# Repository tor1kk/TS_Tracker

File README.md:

# TheftShield_Tracker - GPS tracker with SMS communication 

## Brief

TheftShield Tracker is a device designed to provide real-time tracking and monitoring capabilities for valuable assets or vehicles. It leverages the power of GPS technology, GSM communication, and a microcontroller to offer a comprehensive solution for theft prevention and location tracking.

## Usage Instructions

To use the TheftShield Tracker, follow these steps:

1. **Insert SIM Card**:
    - Insert a nano SIM card into the SIM card slot of the device. Ensure that the SIM card does not have a PIN code set.

2. **Restart the Module**:
    - Restart the module by shorting the NRST and GND pins. This will reset the device and prepare it for operation.

3. **Wait for GPS Initialization**:
    - After restarting, the module will wait until the GPS module acquires a valid location fix. This might take a few minutes, especially in a new location or if the device has been off for a long time.

4. **GSM Module Network Registration**:
    - The GSM module will begin registering with the network. You can monitor the registration process by observing the LED indicator on the module:
        - **Fast blinking** (once every second): The module is searching for or trying to connect to a network.
        - **Slow blinking** (once every 3 seconds): The module is connected to the network.

5. **Send Commands**:
    - Once the device is connected to the network, you can start sending SMS commands to it. Note that the first command you send is usually ignored, so you might need to send it a second time.
    
## Features

The TheftShield Tracker offers the following key features:

- **GPS Tracking**: The device is equipped with a NEO-6M GPS module from u-blox, allowing it to accurately determine its geographic coordinates (latitude and longitude). The NEO-6M is a high-performance GPS receiver with excellent sensitivity and low power consumption.
- **GSM Communication**: The SIM800C GSM module from SIMCOM enables the device to send and receive SMS messages, facilitating remote control and data transmission. The SIM800C is a quad-band GSM/GPRS module that supports voice, SMS, and data transfer.
- **Real-Time Location Updates**: Upon receiving an SMS command, the device can promptly send its current GPS coordinates to a specified phone number.
- **Battery Voltage Monitoring**: The device can measure and report the battery voltage level to a specified phone number, ensuring timely monitoring of the power supply. It uses the built-in Analog-to-Digital Converter (ADC) of the STM32F401RCT6 microcontroller to measure the battery voltage.
- **RTC Alarm Configuration**: Users can set an alarm time through an SMS command. When the alarm triggers, the device will automatically send its GPS coordinates to a predefined phone number. The device utilizes the Real-Time Clock (RTC) peripheral of the STM32F401RCT6 microcontroller to set and manage the alarm.
- **Alarm Time Management**: The device allows users to request the current configured alarm time or deactivate the alarm through SMS commands.
- **Power Management**: The device can enter low-power sleep mode when idle, conserving battery life and extending operational duration. The STM32F401RCT6 microcontroller supports various low-power modes, allowing the device to minimize power consumption when not actively performing tasks.

**Here's a table of the supported SMS commands:**

| Command              | Format           | Description                                                                                         |
|----------------------|------------------|-----------------------------------------------------------------------------------------------------|
| Get GPS Coordinates  | 1:               | Sends the device's current GPS coordinates to the specified phone number.                           |
| Get Voltage          | 2:               | Sends the battery voltage level to the specified phone number.                                      |
| Set Alarm Time       | 3:time:          | Sets the RTC alarm time in 24-hour format (e.g., 3:2359: for 11:59 PM). The device will send GPS coordinates to the specified phone number when the alarm triggers. |
| Get Alarm Time       | 4:               | Requests the currently configured RTC alarm time.                                                   |
| Deactivate Alarm     | 5:               | Deactivates the RTC alarm.                                                                          |

The device is powered by a backup battery and incorporates power management features to extend its operational lifetime. It utilizes the FreeRTOS real-time operating system to manage tasks and ensure efficient resource allocation.

With its combination of GPS tracking, GSM communication, and remote control capabilities, the TheftShield Tracker offers a reliable and versatile solution for asset tracking, theft prevention, and location monitoring applications.

## Photos

### 3D Model

### Real PCB

<br/> 

# Project Structure

The project is organized into two main parts:

TheftShield_Tracker/<br/>
├── hardware/<br/>
│ └── README.md<br/>
└── software/<br/>
│└── README.md<br/>
└──
### hardware/
- **README.md**: Contains information about the hardware design.

### software/
- **README.md**: Contains information about the software implementation.

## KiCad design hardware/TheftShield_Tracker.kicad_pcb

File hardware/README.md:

# Hardware

## Brief

This directory contains the hardware design files for the TheftShield_Tracker project. The project utilizes the following key components:

**Microcontroller**

- STM32F401RCT6 - An ARM Cortex-M4 32-bit microcontroller from STMicroelectronics. It serves as the main control unit, handling task scheduling, communication with peripherals, and executing the application logic.

**GPS Module**

- NEO-6M - A high-performance GPS receiver module from u-blox. It provides accurate positioning data and enables tracking capabilities.

**GSM/GPRS Module**

- SIM800C - A quad-band GSM/GPRS module from SIMCOM. It enables SMS communication for remote control and data transmission.

**Other Components**

- MCP1700 - A low-dropout voltage regulator for providing a stable 3.3V supply.
- Backup battery holder and protection circuitry.
- Assorted passive components (resistors, capacitors, etc.).

## Design Files

- The KiCad project files containing the complete hardware design.
- [GPS tracker schematic](./TheftShield_Tracker.pdf) - A PDF version of the schematic.

## Block diagram

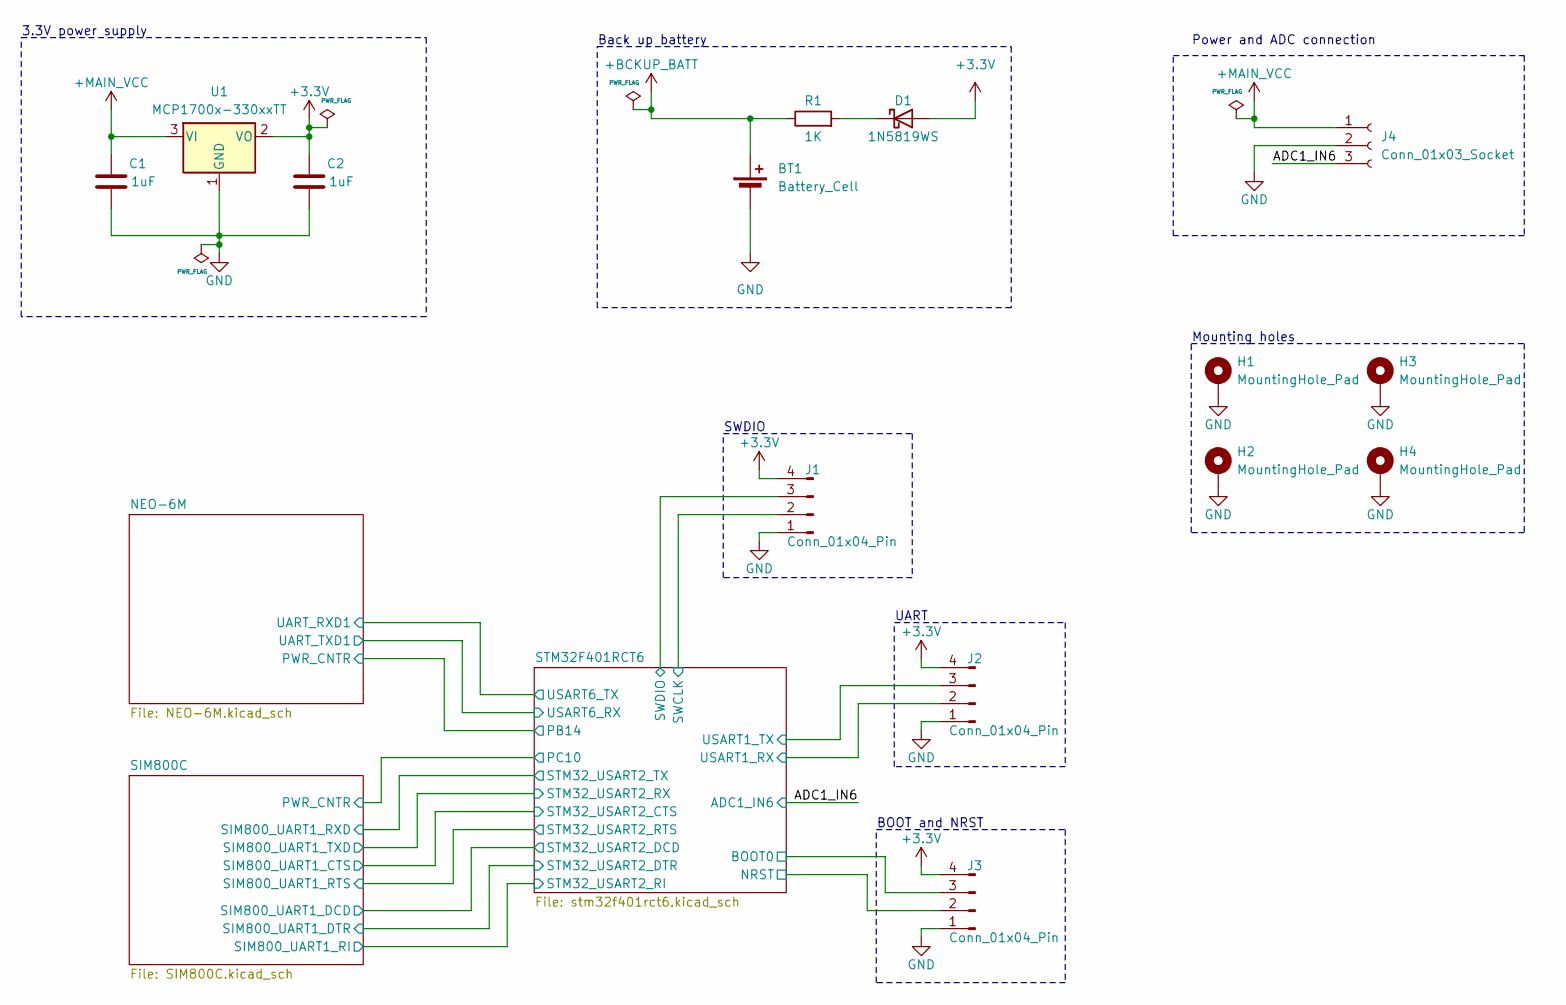
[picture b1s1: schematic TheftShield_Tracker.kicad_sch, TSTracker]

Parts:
BT1: Battery_Cell; SEIKO_ML414H_IV01E
C1, C2: 1uF; C_0805_2012Metric
D1: 1N5819WS; D_SOD-323
H1, H2, H3, H4: MountingHole_Pad; MountingHole_2.2mm_M2_Pad
J1, J2, J3: Conn_01x04_Pin; PinHeader_1x04_P2.54mm_Vertical
J4: Conn_01x03_Socket; JST_XH_B3B-XH-AM_1x03_P2.50mm_Vertical
R1: 1K; R_0603_1608Metric
U1: MCP1700x-330xxTT; SOT-23

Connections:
+3.3V: C2.2, D1.2 (A), J1.4, J2.4, J3.4, U1.2 (VO); also elsewhere on the board
+BCKUP_BATT: BT1.1 (+), R1.1; also elsewhere on the board
+MAIN_VCC: C1.2, J4.1, U1.3 (VI); also elsewhere on the board
/ADC1_IN6: J4.3; also elsewhere on the board
/STM32F401RCT6/BOOT0: J3.3; also elsewhere on the board
/STM32F401RCT6/NRST: J3.2; also elsewhere on the board
/STM32F401RCT6/SWCLK: J1.2; also elsewhere on the board
/STM32F401RCT6/SWDIO: J1.3; also elsewhere on the board
/STM32F401RCT6/USART1_RX: J2.2; also elsewhere on the board
/STM32F401RCT6/USART1_TX: J2.3; also elsewhere on the board
GND: BT1.2 (-), C1.1, C2.1, H1.1, H2.1, H3.1, H4.1, J1.1, J2.1, J3.1, J4.2, U1.1 (GND); also elsewhere on the board
unnamed: D1.1 (K), R1.2

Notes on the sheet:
Power and ADC connection
BOOT and NRST
Mounting holes
SWDIO
Back up battery
3.3V power supply
UART

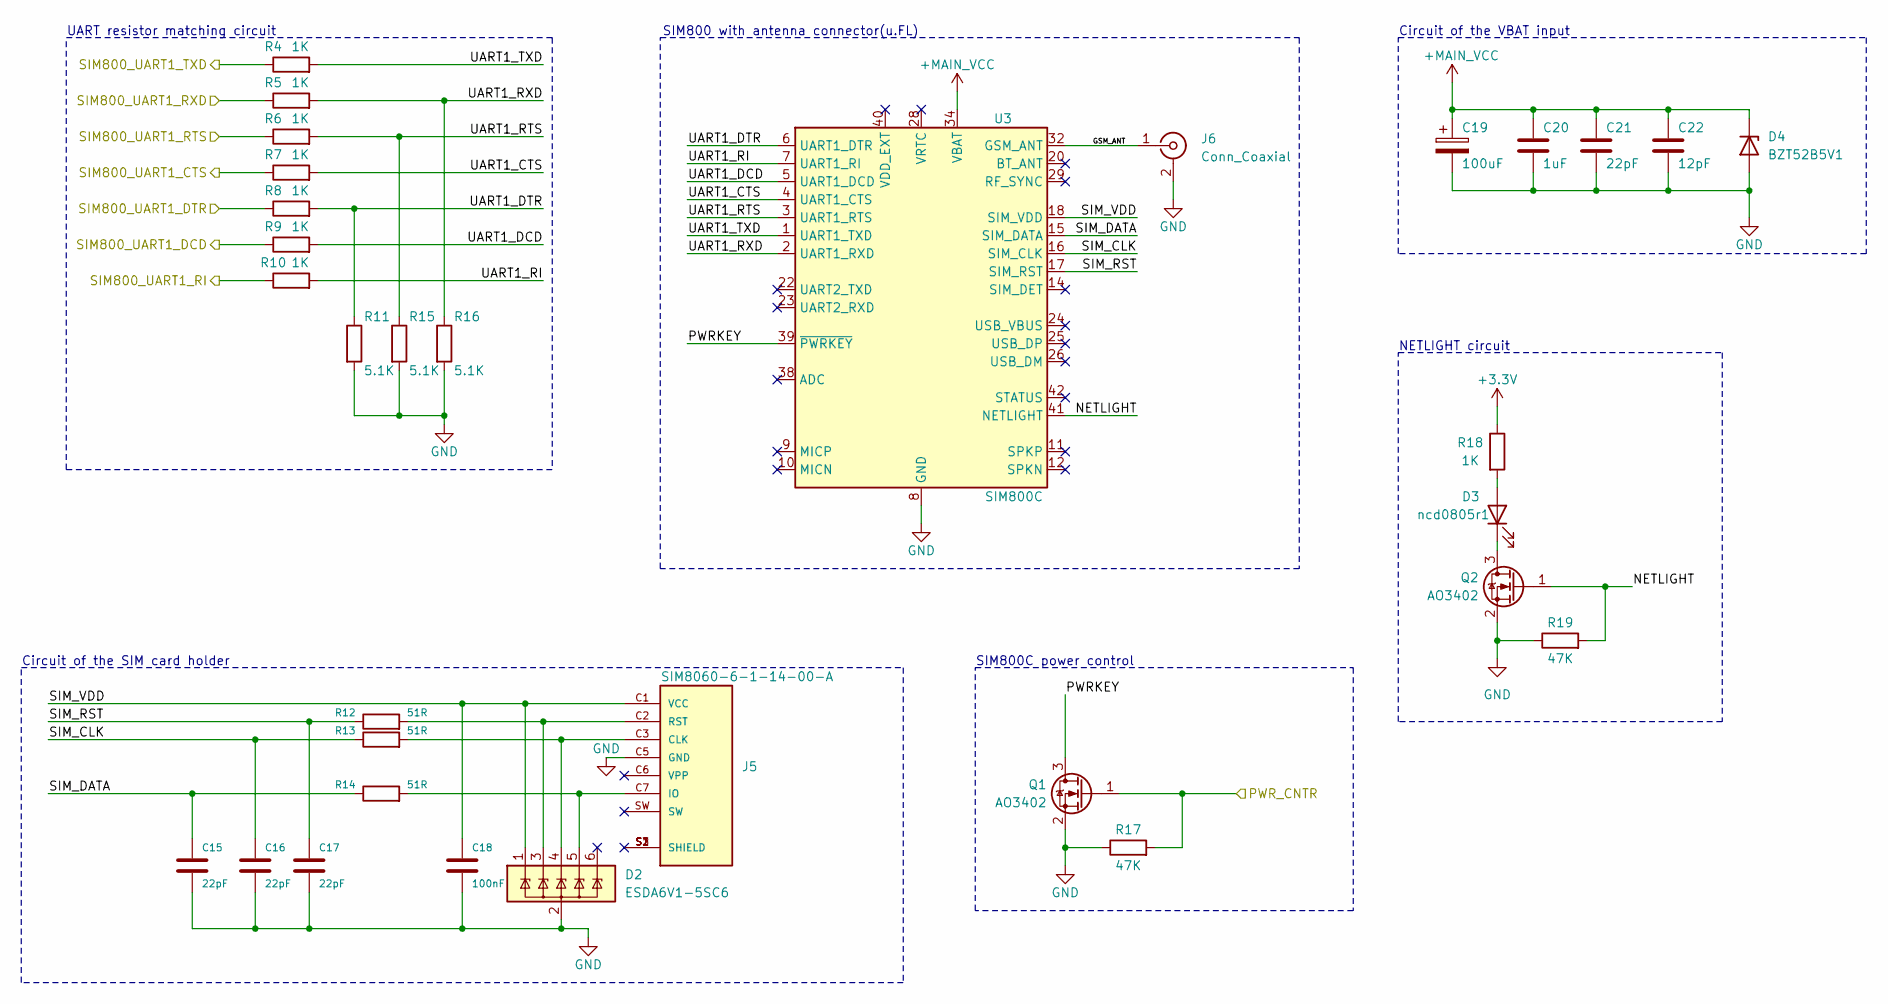
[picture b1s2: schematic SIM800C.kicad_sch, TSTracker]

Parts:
C15, C16, C17, C21: 22pF; C_0603_1608Metric
C18: 100nF; C_0805_2012Metric
C19: 100uF; CP_EIA-3528-21_Kemet-B
C20: 1uF; C_0805_2012Metric
C22: 12pF; C_0603_1608Metric
D2: ESDA6V1-5SC6; SOT-23-6
D3: ncd0805r1; LED_0805_2012Metric
D4: BZT52B5V1; D_SOD-123F
J5: SIM8060-6-1-14-00-A; GCT_SIM8060-6-1-14-00-A; PARTREV A
J6: Conn_Coaxial; U.FL_Hirose_U.FL-R-SMT-1_Vertical
Q1, Q2: AO3402; SOT-23
R4, R5, R6, R7, R8, R9, R10, R18: 1K; R_0603_1608Metric
R11, R15, R16: 5.1K; R_0603_1608Metric
R12, R13, R14: 51R; R_0603_1608Metric
R17, R19: 47K; R_0603_1608Metric
U3: SIM800C; SIMCom_SIM800C

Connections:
+3.3V: R18.1; also elsewhere on the board
+MAIN_VCC: C19.1, C20.1, C21.1, C22.1, D4.1 (K), U3.34 (VBAT), U3.35 (VBAT); also elsewhere on the board
/SIM800C/GSM_ANT: J6.1 (In), U3.32 (GSM_ANT)
/SIM800C/NETLIGHT: Q2.1 (G), R19.2, U3.41 (NETLIGHT)
/SIM800C/PWRKEY: Q1.3 (D), U3.39 (~PWRKEY)
/SIM800C/PWR_CNTR: Q1.1 (G), R17.2; also elsewhere on the board
/SIM800C/SIM_CLK: C16.1, R13.1, U3.16 (SIM_CLK)
/SIM800C/SIM_DATA: C15.1, R14.1, U3.15 (SIM_DATA)
/SIM800C/SIM_RST: C17.1, R12.1, U3.17 (SIM_RST)
/SIM800C/SIM_VDD: C18.1, D2.1 (IO1), J5.C1 (VCC), U3.18 (SIM_VDD)
/SIM800C/UART1_CTS: R7.2, U3.4 (UART1_CTS)
/SIM800C/UART1_DCD: R9.2, U3.5 (UART1_DCD)
/SIM800C/UART1_DTR: R8.2, R11.1, U3.6 (UART1_DTR)
/SIM800C/UART1_RI: R10.2, U3.7 (UART1_RI)
/SIM800C/UART1_RTS: R6.2, R15.1, U3.3 (UART1_RTS)
/SIM800C/UART1_RXD: R5.2, R16.1, U3.2 (UART1_RXD)
/SIM800C/UART1_TXD: R4.2, U3.1 (UART1_TXD)
/STM32F401RCT6/PA0: R7.1; also elsewhere on the board
/STM32F401RCT6/PA1: R6.1; also elsewhere on the board
/STM32F401RCT6/PA2: R5.1; also elsewhere on the board
/STM32F401RCT6/PA3: R4.1; also elsewhere on the board
/STM32F401RCT6/PA4: R10.1; also elsewhere on the board
/STM32F401RCT6/PB10: R8.1; also elsewhere on the board
/STM32F401RCT6/PC5: R9.1; also elsewhere on the board
GND: C15.2, C16.2, C17.2, C18.2, C19.2, C20.2, C21.2, C22.2, D2.2 (GND), D4.2 (A), J5.C5 (GND), J6.2 (Ext), Q1.2 (S), Q2.2 (S), R11.2, R15.2, R16.2, R17.1, R19.1, U3.8 (GND), U3.13 (GND), U3.19 (GND), U3.21 (GND), U3.27 (GND), U3.30 (GND), U3.31 (GND), U3.33 (GND), U3.36 (GND), U3.37 (GND); also elsewhere on the board
unnamed: D2.3 (IO2), J5.C2 (RST), R12.2
unnamed: D2.4 (IO3), J5.C3 (CLK), R13.2
unnamed: D2.5 (IO4), J5.C7 (IO), R14.2
unnamed: D3.2 (A), R18.2
unnamed: D3.1 (K), Q2.3 (D)

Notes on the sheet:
NETLIGHT circuit
Circuit of the VBAT input
UART resistor matching circuit
Circuit of the SIM card holder
SIM800 with antenna connector(u.FL)
SIM800C power control

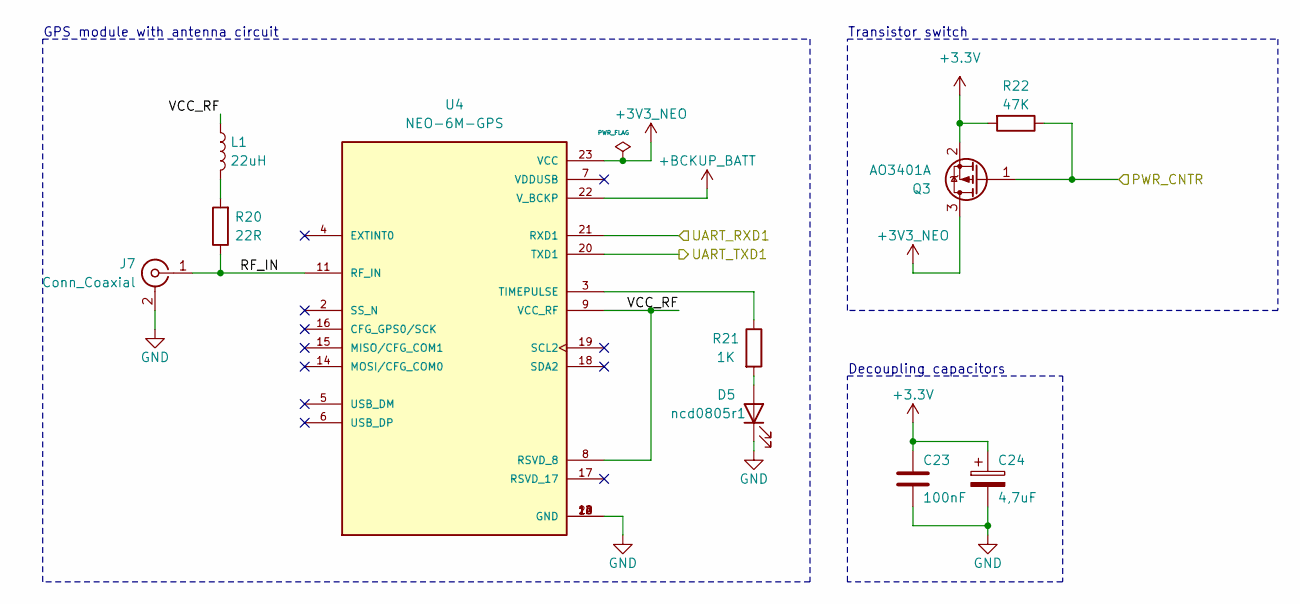
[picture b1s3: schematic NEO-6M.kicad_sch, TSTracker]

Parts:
C23: 100nF; C_0805_2012Metric
C24: 4,7uF; CP_EIA-3216-18_Kemet-A
D5: ncd0805r1; LED_0805_2012Metric
J7: Conn_Coaxial; U.FL_Hirose_U.FL-R-SMT-1_Vertical
L1: 22uH; L_0805_2012Metric
Q3: AO3401A; SOT-23
R20: 22R; R_0603_1608Metric
R21: 1K; R_0603_1608Metric
R22: 47K; R_0603_1608Metric
U4: NEO-6M-GPS; XCVR_NEO-6M-GPS; PARTREV R15

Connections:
+3.3V: C23.1, C24.1, Q3.2 (S), R22.2; also elsewhere on the board
+3V3_NEO: Q3.3 (D), U4.23 (VCC)
+BCKUP_BATT: U4.22 (V_BCKP); also elsewhere on the board
/NEO-6M/PWR_CNTR: Q3.1 (G), R22.1; also elsewhere on the board
/NEO-6M/RF_IN: J7.1 (In), R20.1, U4.11 (RF_IN)
/NEO-6M/UART_RXD1: U4.21 (RXD1); also elsewhere on the board
/NEO-6M/UART_TXD1: U4.20 (TXD1); also elsewhere on the board
/NEO-6M/VCC_RF: L1.1, U4.8 (RSVD_8), U4.9 (VCC_RF)
GND: C23.2, C24.2, D5.1 (K), J7.2 (Ext), U4.10 (GND), U4.12 (GND), U4.13 (GND), U4.24 (GND); also elsewhere on the board
unnamed: D5.2 (A), R21.2
unnamed: L1.2, R20.2
unnamed: R21.1, U4.3 (TIMEPULSE)

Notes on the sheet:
Decoupling capacitors
GPS module with antenna circuit
Transistor switch

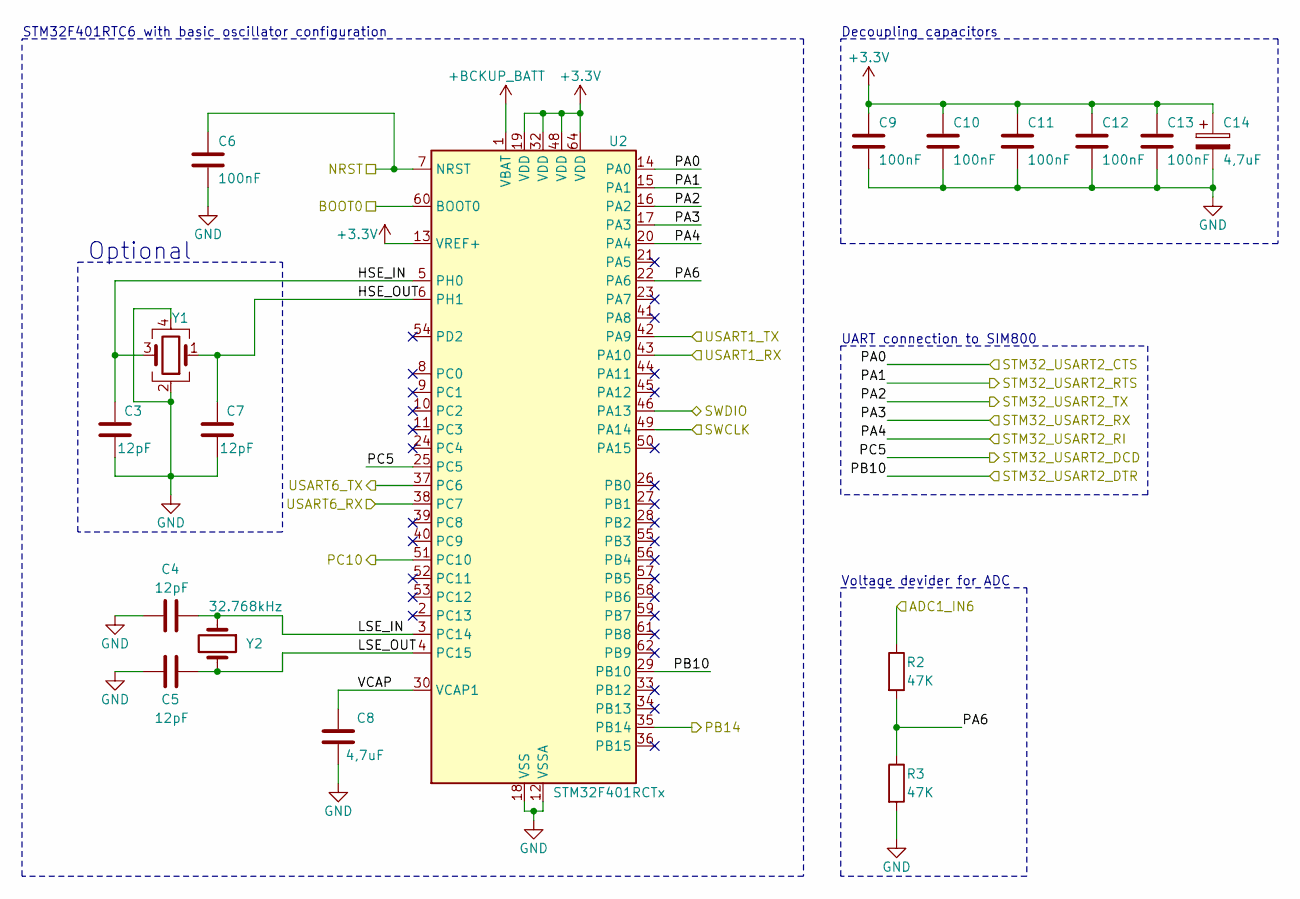
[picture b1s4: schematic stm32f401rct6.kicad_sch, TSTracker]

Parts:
C3, C4, C5, C7: 12pF; C_0603_1608Metric
C6, C9, C10, C11, C12, C13: 100nF; C_0805_2012Metric
C8: 4,7uF; C_0603_1608Metric
C14: 4,7uF; CP_EIA-3216-18_Kemet-A
R2, R3: 47K; R_0603_1608Metric
U2: STM32F401RCTx; LQFP-64_10x10mm_P0.5mm
Y1: Crystal_GND24; Crystal_SMD_3225-4Pin_3.2x2.5mm
Y2: 32.768kHz; Crystal_SMD_3215-2Pin_3.2x1.5mm

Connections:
+3.3V: C9.1, C10.1, C11.1, C12.1, C13.1, C14.1, U2.13 (VREF+), U2.19 (VDD), U2.32 (VDD), U2.48 (VDD), U2.64 (VDD); also elsewhere on the board
+BCKUP_BATT: U2.1 (VBAT); also elsewhere on the board
/ADC1_IN6: R2.1; also elsewhere on the board
/NEO-6M/PWR_CNTR: U2.35 (PB14); also elsewhere on the board
/NEO-6M/UART_RXD1: U2.37 (PC6); also elsewhere on the board
/NEO-6M/UART_TXD1: U2.38 (PC7); also elsewhere on the board
/SIM800C/PWR_CNTR: U2.51 (PC10); also elsewhere on the board
/STM32F401RCT6/BOOT0: U2.60 (BOOT0); also elsewhere on the board
/STM32F401RCT6/HSE_IN: C3.2, U2.5 (PH0), Y1.3
/STM32F401RCT6/HSE_OUT: C7.2, U2.6 (PH1), Y1.1
/STM32F401RCT6/LSE_IN: C4.2, U2.3 (PC14), Y2.1
/STM32F401RCT6/LSE_OUT: C5.2, U2.4 (PC15), Y2.2
/STM32F401RCT6/NRST: C6.1, U2.7 (NRST); also elsewhere on the board
/STM32F401RCT6/PA0: U2.14 (PA0); also elsewhere on the board
/STM32F401RCT6/PA1: U2.15 (PA1); also elsewhere on the board
/STM32F401RCT6/PA2: U2.16 (PA2); also elsewhere on the board
/STM32F401RCT6/PA3: U2.17 (PA3); also elsewhere on the board
/STM32F401RCT6/PA4: U2.20 (PA4); also elsewhere on the board
/STM32F401RCT6/PA6: R2.2, R3.1, U2.22 (PA6)
/STM32F401RCT6/PB0: U2.26 (PB0)
/STM32F401RCT6/PB1: U2.27 (PB1)
/STM32F401RCT6/PB10: U2.29 (PB10); also elsewhere on the board
/STM32F401RCT6/PC5: U2.25 (PC5); also elsewhere on the board
/STM32F401RCT6/SWCLK: U2.49 (PA14); also elsewhere on the board
/STM32F401RCT6/SWDIO: U2.46 (PA13); also elsewhere on the board
/STM32F401RCT6/USART1_RX: U2.43 (PA10); also elsewhere on the board
/STM32F401RCT6/USART1_TX: U2.42 (PA9); also elsewhere on the board
/STM32F401RCT6/VCAP: C8.2, U2.30 (VCAP1)
GND: C3.1, C4.1, C5.1, C6.2, C7.1, C8.1, C9.2, C10.2, C11.2, C12.2, C13.2, C14.2, R3.2, U2.12 (VSSA), U2.18 (VSS), U2.31 (VSS), U2.47 (VSS), U2.63 (VSS), Y1.2, Y1.4; also elsewhere on the board

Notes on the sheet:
Optional
Decoupling capacitors
STM32F401RTC6 with basic oscillator configuration
UART connection to SIM800
Voltage devider for ADC

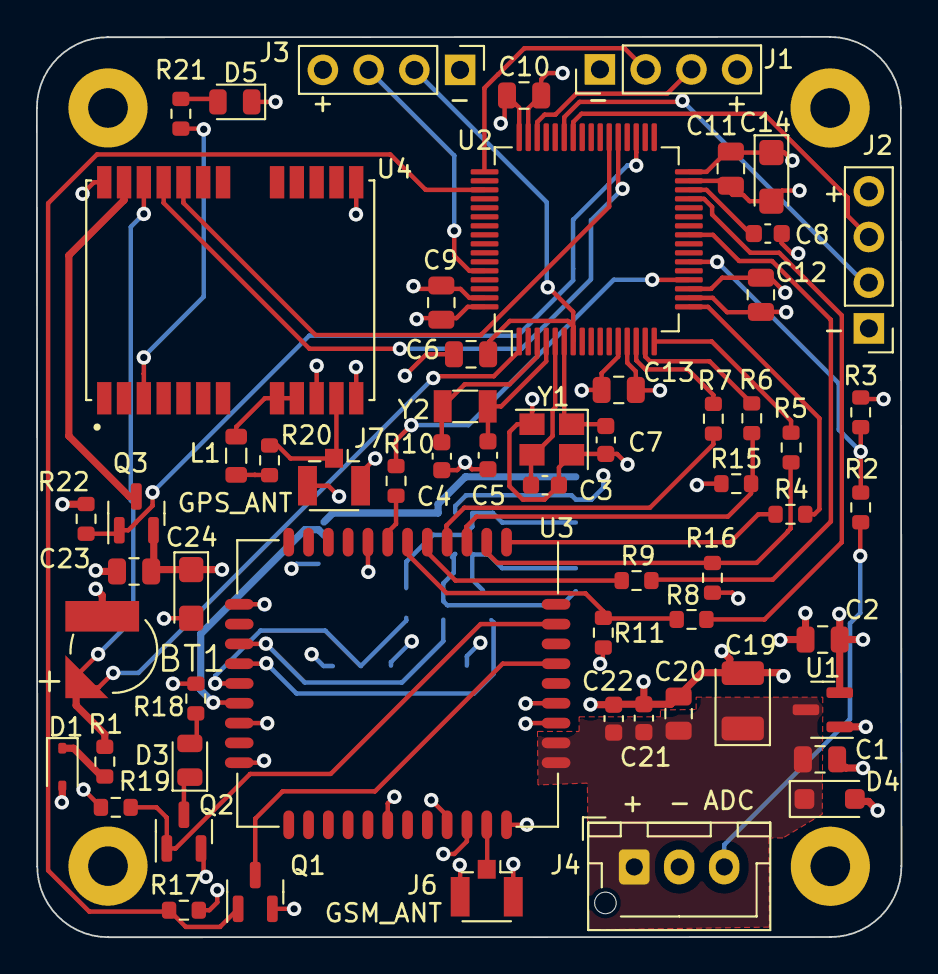
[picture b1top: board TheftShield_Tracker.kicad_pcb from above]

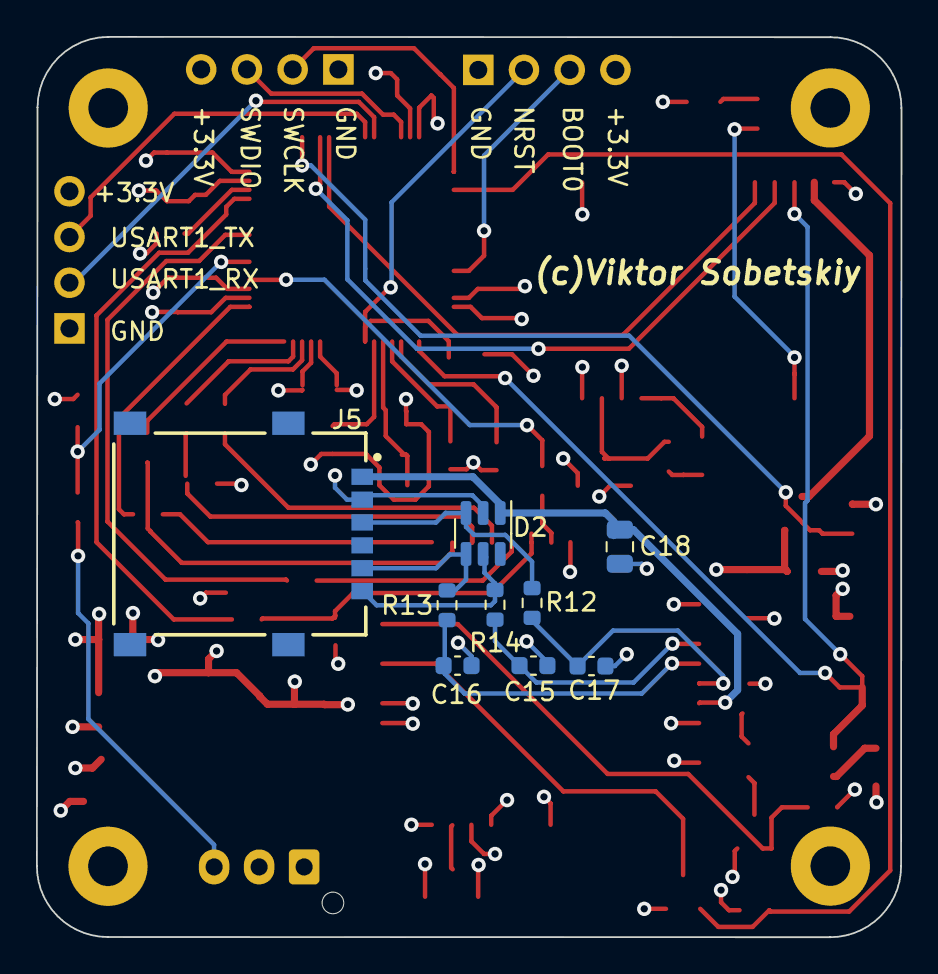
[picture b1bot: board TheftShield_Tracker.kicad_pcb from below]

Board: 4 copper layers, 48.0 x 50.0 mm, 73 parts (9 on the bottom side), 54 nets.

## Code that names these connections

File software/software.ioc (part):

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Mcu.Name=STM32F401R(B-C)Tx
Mcu.Package=LQFP64
Mcu.UserName=STM32F401RCTx
PA10.Mode=Asynchronous
PA10.Signal=USART1_RX
PA13.Signal=SYS_JTMS-SWDIO
PA14.Signal=SYS_JTCK-SWCLK
PA2.Mode=Asynchronous
PA2.Signal=USART2_TX
PA3.Mode=Asynchronous
PA3.Signal=USART2_RX
PA6.Signal=ADCx_IN6
PA9.Mode=Asynchronous
PA9.Signal=USART1_TX
PB14.GPIOParameters=PinState,GPIO_Label
PB14.GPIO_Label=NEO6_PWR_CNTRL
PB14.PinState=GPIO_PIN_SET
PB14.Signal=GPIO_Output
PC10.GPIOParameters=GPIO_Speed,GPIO_Label
PC10.GPIO_Label=SIM_PWR_CNTRL
PC10.GPIO_Speed=GPIO_SPEED_FREQ_HIGH
PC10.Signal=GPIO_Output
PC14-OSC32_IN.Mode=LSE-External-Oscillator
PC14-OSC32_IN.Signal=RCC_OSC32_IN
PC15-OSC32_OUT.Mode=LSE-External-Oscillator
PC15-OSC32_OUT.Signal=RCC_OSC32_OUT
PC6.Mode=Asynchronous
PC6.Signal=USART6_TX
PC7.Mode=Asynchronous
PC7.Signal=USART6_RX
RCC.HSE_VALUE=45000000
RCC.SYSCLKFreq_VALUE=16000000
board=custom

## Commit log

2024-06-30 hardware diagram fix
2024-07-23 Create LICENSE
